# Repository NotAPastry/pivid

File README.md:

# PiVid v2.1

A low-latency H.264 video link between two Raspberry Pi Zero 2 W boards over a
NiceRF LR2021 S-band radio running FLRC at 2.1 GHz.

The transmit Pi encodes camera video with `rpicam-vid` and fragments it onto the
radio. The receive Pi reassembles the stream and hands it to a caster, which
distributes it over the LAN to one or more desktop players; the receive Pi can
also drive a local HDMI or composite display directly.

Measured event-to-eyeball latency is **~150 ms median** (TX camera scene to RX
HDMI monitor, motion video at 950 kbps, filmed at 240 fps, n=132). About 35–40 ms
of that is the PiVid pipeline itself; the rest is camera and display physics. See
[docs/MEASUREMENTS.md](docs/MEASUREMENTS.md).

## Architecture

```
 +-------------+  H.264 bytes   +----------+  ring   +----------------+
 | rpicam-vid  | ──────────────▶│ pivid-tx │────────▶│ lr2021.ko (TX) │
 +-------------+   (stdin)      +----------+  mmap   +-------+--------+
                                                             │ SPI
                                              LR2021 radio (FLRC, 2.1 GHz)
                                                             │
                          ring   +----------+  pipe  +-----------+
 lr2021.ko (RX) ─────────────────▶│ pivid-rx │──────▶│pivid-caster│
 +--------------+           mmap   +----------+       +-----+------+
                                                            │ LAN (UDP video + telemetry)
                                                            ▼
                                                    +---------------+
                                                    | pivid-player  |  decode + OSD
                                                    | (Mac/Linux/Win)|  on the viewer
                                                    +---------------+
```

The repo holds one kernel driver, five userspace programs and a shared library:

| Path | Role |
|------|------|
| `drivers/lr2021/` | Thin SPI/IRQ proxy. Owns the SPI state machine, BUSY pin polling, threaded DIO9 interrupt, two mmap'd SPSC ring buffers, and a small ioctl surface. Exposes `/dev/radio0`. |
| `apps/pivid-tx/` | TX daemon. Reads Annex-B H.264 from stdin, fragments into 0–253-byte payloads with a 1-byte flags/SEQ header, pushes into the TX ring. Handles bind broadcast, bind LED and button. Carries the gated AQM frame-drop stage (`docs/aqm/`). |
| `apps/pivid-rx/` | RX daemon. Drains the RX ring, validates SEQ, reassembles NAL units, and emits the stream to `pivid-caster`, a UDP socket, or a local `gst-launch` sink. Bind-listen, bind LED, button. |
| `apps/pivid-caster/` | Distributes the RX stream over the LAN — accepts player subscriptions and fans out video plus telemetry to one or more viewers. |
| `apps/pivid-player/` | Cross-platform desktop viewer (macOS, Linux; Windows partial). Decodes H.264 in software by default and composites the MSP DisplayPort OSD over it. See `apps/pivid-player/README.md`. |
| `apps/pivid-config-agent/` | On-Pi config and web dashboard (civetweb). Reads and writes `pivid.conf`, applies changes via SIGHUP/modreload tiers, and serves the schema-driven settings UI plus a WPA2 config AP. Never opens `/dev/radio0`. |
| `common/` | Shared static library: protocol and packet helpers, canonical config parse/serialize, binding-phrase → sync-word derivation, apply-tier schema, libgpiod peripherals, ioctl UAPI, userspace ring accessors. |
| `tests/` | Host-side unit tests across `agent/ caster/ common/ driver/ integration/ player/ rx/ scripts/ tx/`, run in a `gcc:bookworm` container, plus `smoke_test.sh` for hardware verification over ssh. |
| `target/` | Files installed **on the Pi** — the path under `target/` is the path on the device (systemd units, `/opt/pivid` helpers, modprobe and modules-load config). |
| `scripts/` | Host-side tooling that never leaves the build machine: `deploy.sh`, the two patched-upstream cross-builds, and the web-asset embedder. |
| `hat/` | KiCad project for the carrier board (Pi Zero µHAT, 4-layer). |

## Hardware

LR2021 module on Pi SPI0:

| Pi GPIO | LR2021 pin | Direction | Notes |
|---------|------------|-----------|-------|
| MOSI/MISO/SCK/CE0 | MOSI/MISO/SCK/NSS | bidirectional | Standard SPI bus |
| GPIO17 | NRESET | output, active-low | Driver pulses to hard-reset |
| GPIO22 | BUSY | input | Driver polls before each SPI frame |
| GPIO27 | DIO9 | input + IRQ | Rising edge triggers the driver IRQ thread |

Peripherals (full pin-by-pin table in `docs/hardware/gpio.txt`):

| GPIO | Purpose |
|------|---------|
| GPIO5 | TX status LED — blinks while data is moving |
| GPIO6 | Bind LED — solid when bound, slow blink during bind, fast blink during new-bind |
| GPIO13 | Bind button — long-press starts the bind procedure |

The TX side can additionally drive an external SZM-2166Y power amplifier
(~36 dB gain, rated 33 dBm / 2 W, 2.3–2.7 GHz) from a 6S pack. The radio's own
output is set to −3 dBm so the amplifier runs at its rated output without input
overdrive. Note the default carrier (2.1 GHz) is **below** that amplifier's rated
band — see [docs/DECISIONS.md](docs/DECISIONS.md) before transmitting with it.

Both Pis are wired identically; the only configuration difference is which side
runs `pivid-tx.service` and which runs `pivid-rx.service`.

## Build, deploy, verify

```sh
make all     # build everything in Docker (tx, rx, caster, config-agent, player, lr2021.ko, lr2021.dtbo)
make tests   # host-side unit tests in a gcc:bookworm container
make deploy  # copy, install and enable services on both Pis (env: TX_HOST, RX_HOST)
make smoke   # hardware verification over ssh against the deployed Pis
```

Starting from bare hardware, prepare the two SD cards first —
[docs/SD_CARD.md](docs/SD_CARD.md) covers flashing the DietPi image and applying
the per-role boot config.

The Pis have no native compiler — everything cross-builds on the host or in
Docker into `bin/`, and `deploy.sh` copies the ARM binaries over. A first install
needs one reboot to pick up the device-tree overlay; see
[docs/DEPLOY.md](docs/DEPLOY.md).

## Documentation

- [docs/SD_CARD.md](docs/SD_CARD.md) — flashing the DietPi image and applying the per-role boot config
- [docs/BUILD.md](docs/BUILD.md) — Docker image, make targets, kernel pinning
- [docs/DEPLOY.md](docs/DEPLOY.md) — deploy, first-install reboot, smoke test, settings, bind, troubleshooting
- [docs/DECISIONS.md](docs/DECISIONS.md) — settled engineering decisions and the constraints behind them
- [docs/MEASUREMENTS.md](docs/MEASUREMENTS.md) — measured results: latency budget, RF and SPI campaigns, FEC sweeps
- [docs/protocol/](docs/protocol/) — wire format, packet layout, FEC, reassembly, OSD grid, telemetry, LAN chunking
- [docs/aqm/README.md](docs/aqm/README.md) — feeder-level frame-drop AQM
- [docs/MSP_DISPLAYPORT_OSD.md](docs/MSP_DISPLAYPORT_OSD.md) — MSP DisplayPort OSD relay
- [docs/hardware/gpio.txt](docs/hardware/gpio.txt) — full pin-by-pin wiring table
- [docs/hidden-env-knobs.md](docs/hidden-env-knobs.md) — environment variables not exposed in the UI
- [TODO.md](TODO.md) — open work

## Licence

Copyright (C) 2026 Pi.

- **Software** — GPL-3.0-or-later, plus a section 7(b) term requiring that the
  PiVid attribution be preserved in user-visible notices.
- **Kernel code** (`drivers/lr2021/`, the `bcm2835-codec` patches, and the tests
  that include driver headers) — GPL-2.0-only, as Linux derivative works.
- **Hardware** (`hat/`) — CERN-OHL-P-2.0. Fork it, modify it, sell boards; just
  keep the notices.

You can sell hardware and products built on PiVid. You cannot ship the software
in closed form, and you cannot call your fork "PiVid". See [LICENSE](LICENSE) for
the authoritative per-path map, and a note for distributors about FFmpeg builds.

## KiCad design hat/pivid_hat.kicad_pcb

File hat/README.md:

# PiVid HAT

KiCad project for the PiVid carrier board — a Raspberry Pi Zero µHAT that mounts
the LR2021 radio module and the status LEDs and bind button the daemons drive.

| | |
|---|---|
| Design | `pivid hat v2`, rev 1.0 |
| KiCad | 10.x (`.kicad_sch` / `.kicad_pcb`) |
| Form factor | Raspberry Pi Zero µHAT, 65 × 30 mm, 4 × M2.5 mounting holes |
| Stack-up | 4 layer — `F.Cu`, `In1.Cu` (Power), `In2.Cu` (GND), `B.Cu` |
| Placements | 21 footprints (2 ICs, 3 connectors, 3 LEDs, 3 resistors, 4 capacitors, 1 switch, 1 jumper, 4 mounting holes) |

The GPIO assignments this board implements are documented in
[../docs/hardware/gpio.txt](../docs/hardware/gpio.txt) — SPI0 plus NRESET on
GPIO17, BUSY on GPIO22 and DIO9 on GPIO27 for the radio, and GPIO5 / GPIO6 /
GPIO13 for the TX LED, bind LED and bind button.

## What is tracked

Design sources only:

```
pivid_hat.kicad_pro      project
pivid_hat.kicad_sch      schematic
pivid_hat.kicad_pcb      board layout
fp-lib-table             footprint library table (project-relative)
sym-lib-table            symbol library table (project-relative)
library/                 LoRa2021 symbol, footprint and STEP model
lib.pretty/              mounting holes + the 2x20 µHAT pin socket
```

Everything KiCad regenerates is ignored — see [.gitignore](.gitignore). That
includes gerbers and drill files: **produce fabrication output from the
`.kicad_pcb`** (File → Fabrication Outputs) rather than trusting a checked-in
copy, which silently goes stale the moment the layout changes.

## Attribution

The board outline, mounting-hole placement and the µHAT pin-socket footprint
derive from the **Raspberry Pi Zero (W) uHAT Template Board** by Ravikiran
Bukkasagara, released under the MIT License:

> Copyright (c) 2019 Ravikiran Bukkasagara <contact@ravikiranb.com>
>
> Permission is hereby granted, free of charge, to any person obtaining a copy
> of this software and associated documentation files (the "Software"), to deal
> in the Software without restriction, including without limitation the rights
> to use, copy, modify, merge, publish, distribute, sublicense, and/or sell
> copies of the Software, and to permit persons to whom the Software is
> furnished to do so, subject to the following conditions:
>
> The above copyright notice and this permission notice shall be included in all
> copies or substantial portions of the Software.
>
> THE SOFTWARE IS PROVIDED "AS IS", WITHOUT WARRANTY OF ANY KIND, EXPRESS OR
> IMPLIED, INCLUDING BUT NOT LIMITED TO THE WARRANTIES OF MERCHANTABILITY,
> FITNESS FOR A PARTICULAR PURPOSE AND NONINFRINGEMENT. IN NO EVENT SHALL THE
> AUTHORS OR COPYRIGHT HOLDERS BE LIABLE FOR ANY CLAIM, DAMAGES OR OTHER
> LIABILITY, WHETHER IN AN ACTION OF CONTRACT, TORT OR OTHERWISE, ARISING FROM,
> OUT OF OR IN CONNECTION WITH THE SOFTWARE OR THE USE OR OTHER DEALINGS IN THE
> SOFTWARE.

See the [HAT design guidelines](https://github.com/raspberrypi/hats/blob/master/designguide.md)
for the mechanical and electrical requirements a HAT has to meet. Note this
board carries **no ID EEPROM** — the template omits it deliberately, since the
footprint and pull-up sizing are project-specific.

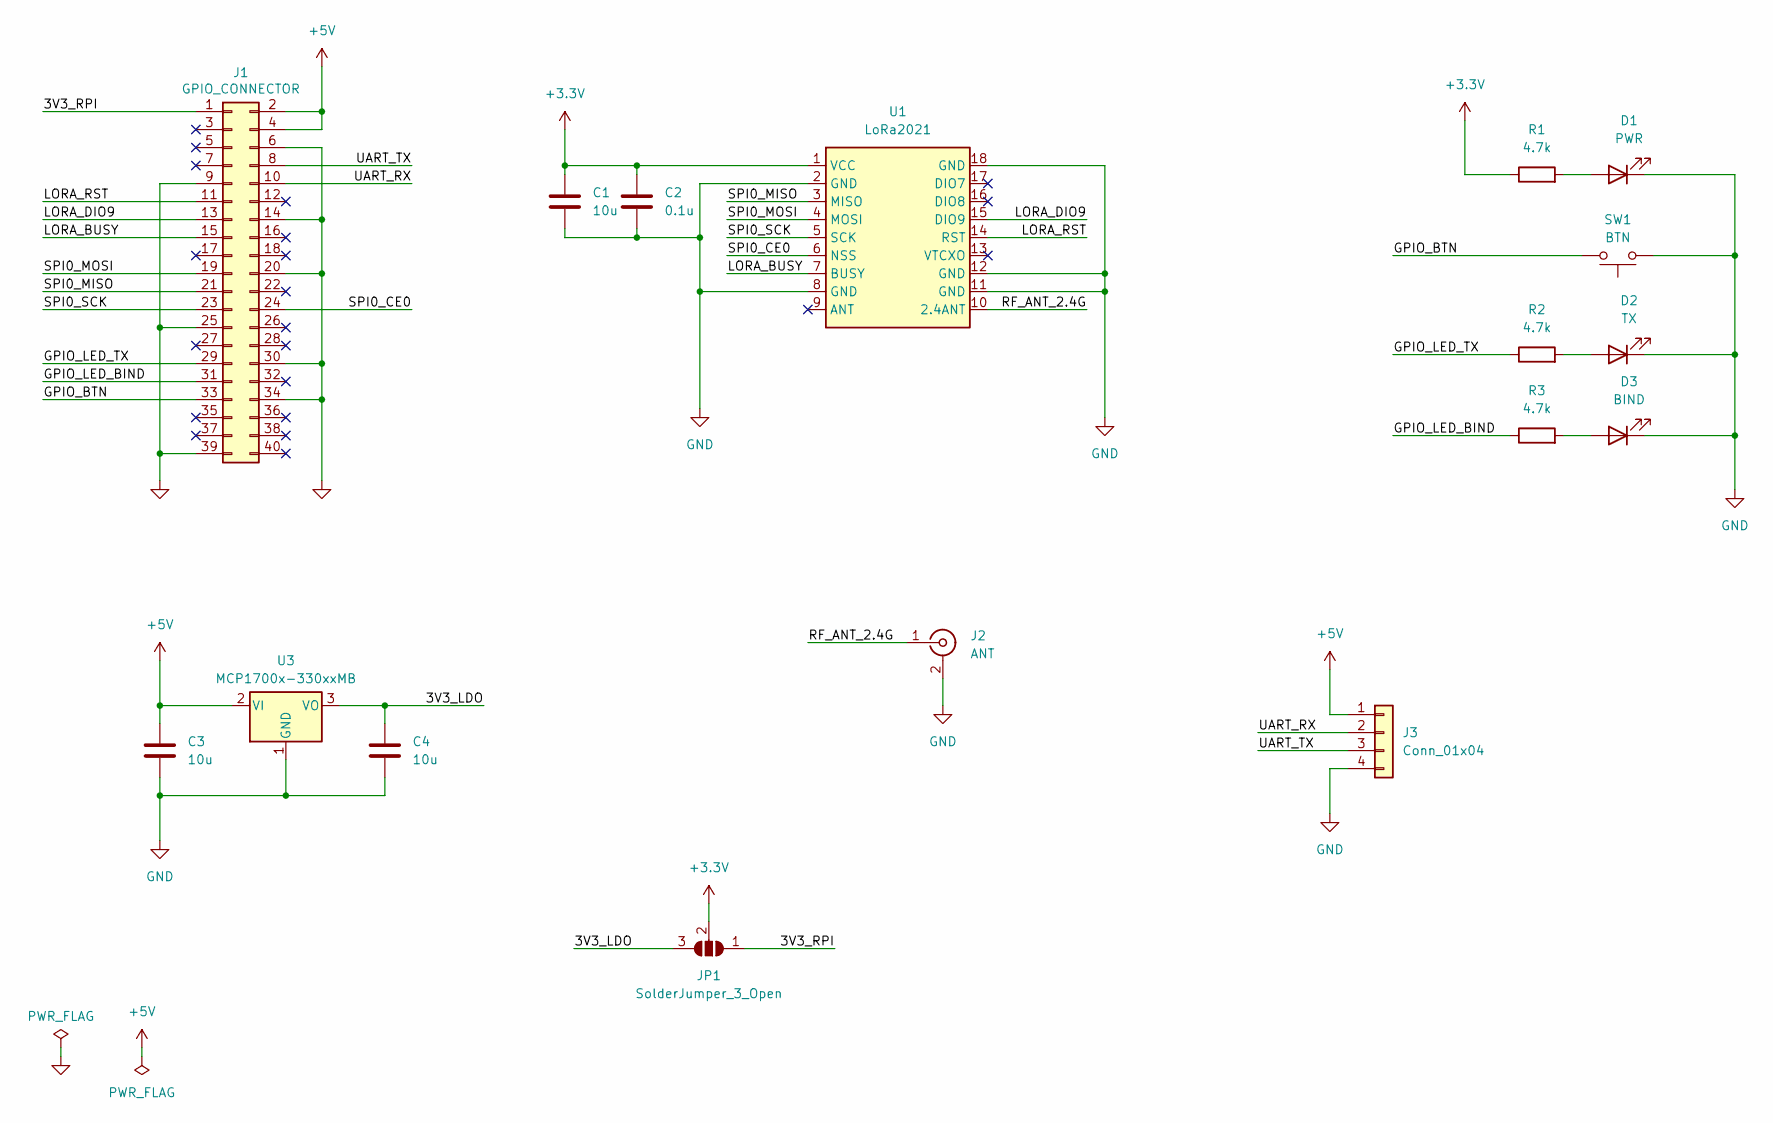
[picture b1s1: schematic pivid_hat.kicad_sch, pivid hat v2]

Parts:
C1, C3, C4: 10u; C_0805_2012Metric_Pad1.18x1.45mm_HandSolder
C2: 0.1u; C_0805_2012Metric_Pad1.18x1.45mm_HandSolder
D1: PWR; LED_0805_2012Metric_Pad1.15x1.40mm_HandSolder
D2: TX; LED_0805_2012Metric_Pad1.15x1.40mm_HandSolder
D3: BIND; LED_0805_2012Metric_Pad1.15x1.40mm_HandSolder
J1: GPIO_CONNECTOR; PinSocket_2x20_P2.54mm_Vertical_Centered_Anchor
J2: ANT; SMA_Molex_73251-1153_EdgeMount_Horizontal
J3: Conn_01x04; JST_SH_SM04B-SRSS-TB_1x04-1MP_P1.00mm_Horizontal
JP1: SolderJumper_3_Open; SolderJumper-3_P1.3mm_Open_RoundedPad1.0x1.5mm_NumberLabels
R1, R2, R3: 4.7k; R_0805_2012Metric_Pad1.20x1.40mm_HandSolder
SW1: BTN; SW_SPST_PTS645Sx43SMTR92
U1: LoRa2021
U3: MCP1700x-330xxMB; SOT-89-3

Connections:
+3.3V: C1.1, C2.1, JP1.2 (C), R1.1, U1.1 (VCC)
+5V: C3.1, J1.2, J1.4, J3.1, U3.2 (VI)
/3V3_LDO: C4.1, JP1.3 (B), U3.3 (VO)
/3V3_RPI: J1.1, JP1.1 (A)
/GPIO_BTN: J1.33, SW1.2
/GPIO_LED_BIND: J1.31, R3.1
/GPIO_LED_TX: J1.29, R2.1
/LORA_BUSY: J1.15, U1.7 (BUSY)
/LORA_DIO9: J1.13, U1.15 (DIO9)
/LORA_RST: J1.11, U1.14 (RST)
/RF_ANT_2.4G: J2.1 (In), U1.10 (2.4ANT)
/SPI0_CE0: J1.24, U1.6 (NSS)
/SPI0_MISO: J1.21, U1.3 (MISO)
/SPI0_MOSI: J1.19, U1.4 (MOSI)
/SPI0_SCK: J1.23, U1.5 (SCK)
/UART_RX: J1.10, J3.2
/UART_TX: J1.8, J3.3
GND: C1.2, C2.2, C3.2, C4.2, D1.1 (K), D2.1 (K), D3.1 (K), J1.6, J1.9, J1.14, J1.20, J1.25, J1.30, J1.34, J1.39, J2.2 (Ext), J3.4, SW1.1, U1.2 (GND), U1.8 (GND), U1.11 (GND), U1.12 (GND), U1.18 (GND), U3.1 (GND)
unnamed: D1.2 (A), R1.2
unnamed: D2.2 (A), R2.2
unnamed: D3.2 (A), R3.2

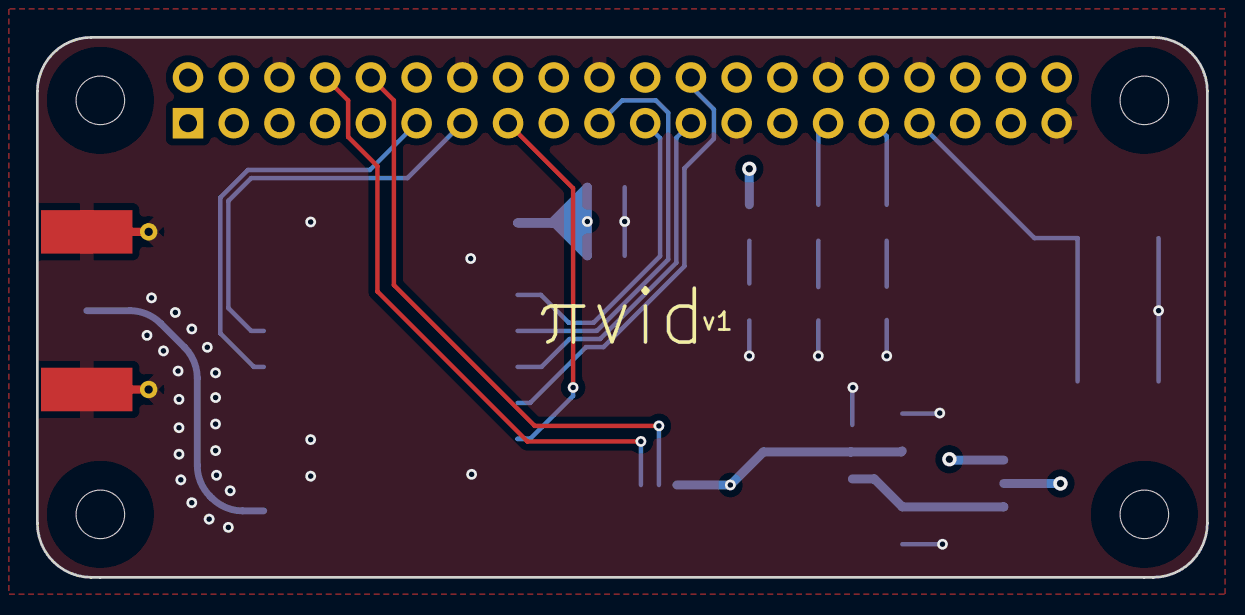
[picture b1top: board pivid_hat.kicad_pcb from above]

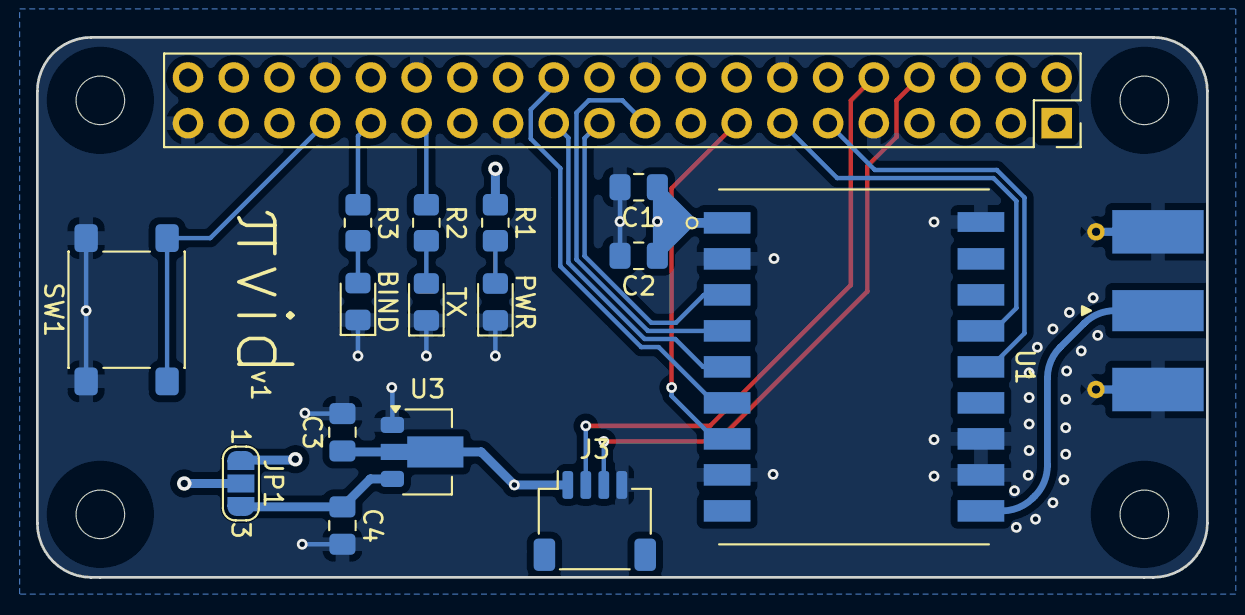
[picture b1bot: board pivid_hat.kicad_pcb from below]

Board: 4 copper layers, 65.0 x 30.0 mm, 21 parts (17 on the bottom side), 21 nets.

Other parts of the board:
H1, H2, H3, H4: MountingHole; MountingHole_2.7mm_M2.5_uHAT_RPi

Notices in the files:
hat/pivid_hat.kicad_pcb:
This PCB design is licensed under MIT Open Source License.
